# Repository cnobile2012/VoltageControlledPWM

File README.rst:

***************************************
Voltage-Controlled PWM Motor Controller
***************************************
The MIT License (MIT)

This circuit can supply either a 3.3 or 5 volt logic level PWM signal
depending on the reference voltage used. The voltage control input can also
be driven with either a 3.3 or 5 volt logic level signal depending on the
how the circuit is calibrated.

The PWM frequency can be adjusted in the range of 25K Hertz.

=======
LTspice
=======

Spice files for testing the circuit viability.

=====
KiCAD
=====

KiCAD files of the schematic and PCB.

========================
Calibration Instructions
========================

Test Equipment
--------------

  1. +12 and -12 Volt bench power supply.
  2. +5 or +3.3 Volt bench power supply.
  3. Variable voltage bench supply (0V-3.3V or 0V-5V).
  4. Multimeter
  5. Oscilloscope
  6. Frequency Counter (Optional--Can use the scope)

First, be sure your dual voltage power supply is as close to +12 and -12 volts
as possible. This will also be true in the actual environment that this PWM
will call home. If there is a slight offset between the absolute + and -
voltages there will also be a slight offset between the internal zero crossing
point of the triangle wave. Resistor R6 (460) can be adjusted to compensate for
this. The two trimmers R9 and R11 can also affect a slightly off zero crossing
by adjusting the complete on or off of the PWM, that is where a 0 control
voltage causes the output PWM to be 0 volts and the max 3.3/5 control voltage
causes the PWM to be 3.3/5 volts.

Calibration
-----------

  1. The R3 trimmer is used to adjust the internal triangle reference voltage.
     This should nominally be 10 volts peak-to-peak with the trimmer set to
     approximately 250K. Put your scope probes between TP2 (Triangle Wave) and
     TP0 (GND) then adjust R3.
  2. The R1 trimmer is used to adjust the frequency of the triangle wave. This
     should nominally be 25K Hertz with the trimmer set to approximately 24K.
     Put your scope or frequency counter probes between TP2 (Triangle Wave)
     and TP0 (GND) then adjust R1.
  3. The R9 trimmer is used to adjust the symmetry of the sweep voltage. This
     is the Control Voltage that adjusts the modulation of the PWM frequency.
     Adjust the variable power supply to 50% of 3.3V (1.65V) or 5V (2.5V)
     depending on your drive voltage then attach the supply to J3 and attach
     the multimeter probes to TP3 (Sweep) and TP0 (GND). Double check that the
     supply voltage is at 50% of your driving voltage then adjust R9 so the
     voltage on the multimeter is as close to 0 (zero) volts as possible.
  4. The R11 trimmer is used to set the peak-to-peak of the sweep voltage. Set
     the variable power supply to your drive voltage 5V or 3.3V and attach it
     to J3 (Voltage Control Input). Attach the multimeter probes to TP3 (Sweep)
     and TP0 (GND). Adjust R11 so that the multimeter shows plus 5V. Adjust the
     supply to 0 (zero) volts (or short the two pins on J3) and check that the
     voltage on the multimeter is -5V. See note 1 below.
  5. Check the PWM. Adjust the supply voltage to 50% as was done in step 3
     above and check that the PWM is 50%, then adjust the supply to 0 (zero)
     (or just short the two pins on J3) Check that the PWM is 0 (zero) volts.

Notes:

  1. In order to get 0 (full off) and 5/3.3 Volts (full on), on the PWM the
     sweep voltage may need to be slightly more than 10V peak-to-peak (R11)
     assuming the maximum triangle wave voltage is still 10V
     peak-to-peak. Adjusting the zero crossing with R9 may also be necessary.
  2. TP1 provides a square wave output, however it is not used in any of the
     calibrations.
  3. On Version 1.0 of the PCB the silk screen for the TPs (test points) are
     rather small and difficult to read. This will be fixed in version 2.0 of
     the PCB. The photos below should help with identifying which TP is which.

==============
PCBs Version 1
==============

.. image:: images/VoltageControlledPWM-V1.0-front.jpg
  :width: 400
  :alt: Circuit board frontside image

.. image:: images/VoltageControlledPWM-V1.0-back.jpg
  :width: 400
  :alt: Circuit board backside image

=========
Schematic
=========

.. image:: images/VoltageControlledPWM-V1.0.png
  :width: 400
  :alt: Schematic

I want to give attribution to `Zero999 <https://www.eevblog.com/forum/beginners/simple-analog-function-generator-design/msg1174983/#msg1174983>`_
for the oscillator part of my circuit.

Feel free to contact me at: carl dot nobile at gmail.com

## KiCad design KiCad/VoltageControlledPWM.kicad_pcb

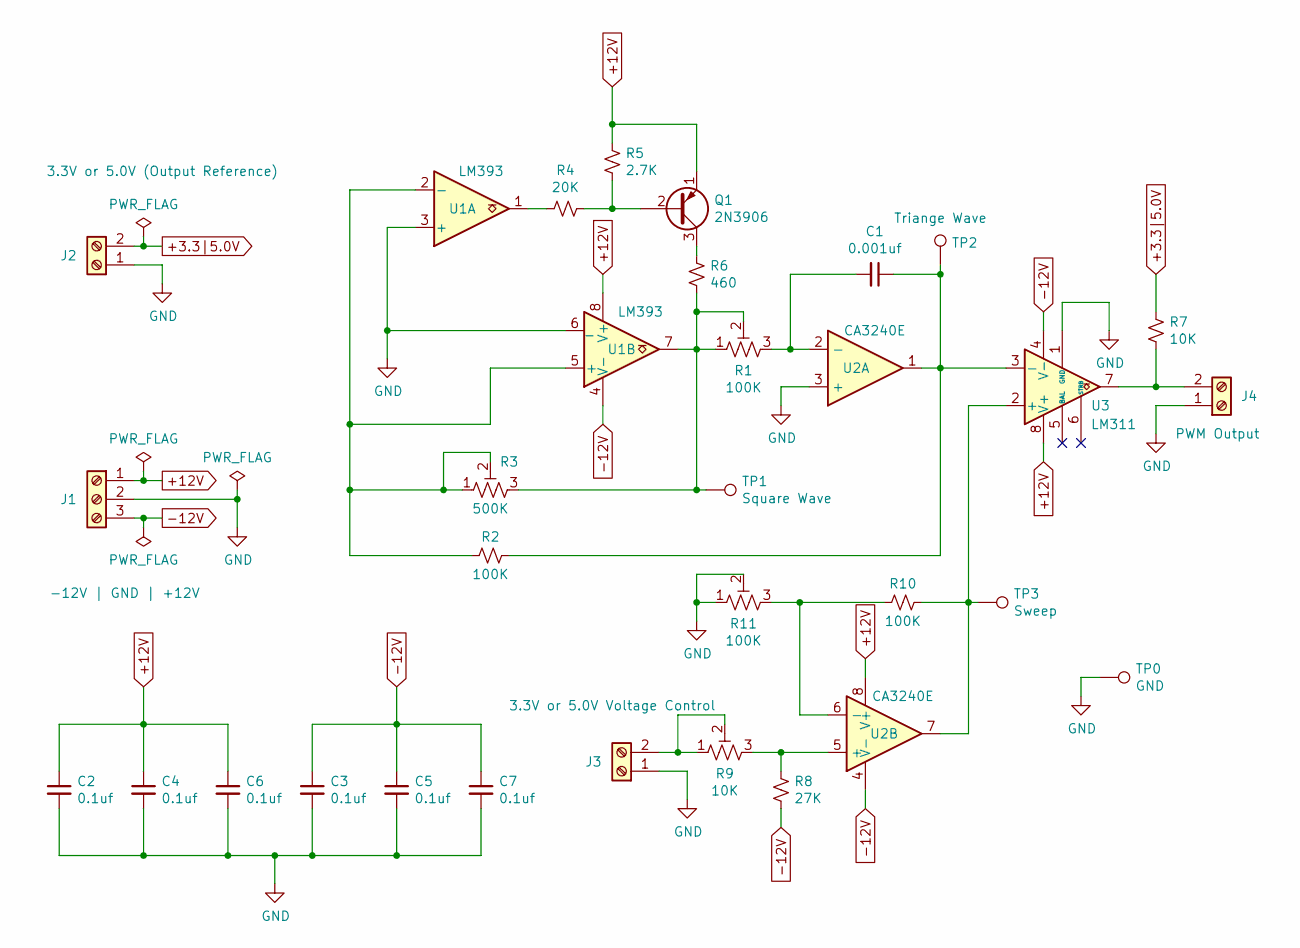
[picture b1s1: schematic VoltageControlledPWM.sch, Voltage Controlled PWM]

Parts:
C1: 0.001uf; C_Disc_D4.7mm_W2.5mm_P5.00mm
C2, C3, C4, C5, C6, C7: 0.1uf; C_Disc_D4.7mm_W2.5mm_P5.00mm
J1: -12V | GND | +12V; TerminalBlock_Phoenix_MKDS-1,5-3-5.08_1x03_P5.08mm_Horizont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
J2: 3.3V or 5.0V (Output Reference); TerminalBlock_Phoenix_MKDS-1,5-2-5.08_1x02_P5.08mm_Horizont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
J3: 3.3V or 5.0V Voltage Control; TerminalBlock_Phoenix_MKDS-1,5-2-5.08_1x02_P5.08mm_Horizont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
J4: PWM Output; TerminalBlock_Phoenix_MKDS-1,5-2-5.08_1x02_P5.08mm_Horizont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
Q1: 2N3906; TO-92_Inline
R1, R11: 100K; Potentiometer_Bourns_3296W_Vertical
R2, R10: 100K; R_Axial_DIN0207_L6.3mm_D2.5mm_P10.16mm_Horizontal
R3: 500K; Potentiometer_Bourns_3296W_Vertical
R4: 20K; R_Axial_DIN0207_L6.3mm_D2.5mm_P10.16mm_Horizontal
R5: 2.7K; R_Axial_DIN0207_L6.3mm_D2.5mm_P10.16mm_Horizontal
R6: 460; R_Axial_DIN0207_L6.3mm_D2.5mm_P10.16mm_Horizontal
R7: 10K; R_Axial_DIN0207_L6.3mm_D2.5mm_P10.16mm_Horizontal
R8: 27K; R_Axial_DIN0207_L6.3mm_D2.5mm_P10.16mm_Horizontal
R9: 10K; Potentiometer_Bourns_3296W_Vertical
TP0: GND; TestPoint_Loop_D2.50mm_Drill1.0mm
TP1: Square Wave; TestPoint_Loop_D2.50mm_Drill1.0mm
TP2: Triange Wave; TestPoint_Loop_D2.50mm_Drill1.0mm
TP3: Sweep; TestPoint_Loop_D2.50mm_Drill1.0mm
U1: LM393; SO-8_3.9x4.9mm_P1.27mm
U2: CA3240E; DIP-8_W7.62mm
U3: LM311; DIP-8_W7.62mm

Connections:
+3.3|5.0V: J2.2, R7.1
+12V: C2.1, C4.1, C6.1, J1.1, Q1.1 (E), R5.1, U1.8 (V+), U2.8 (V+), U3.8 (V+)
-12V: C3.1, C5.1, C7.1, J1.3, R8.2, U1.4 (V-), U2.4 (V-), U3.4 (V-)
GND: C2.2, C3.2, C4.2, C5.2, C6.2, C7.2, J1.2, J2.1, J3.1, J4.1, R11.1, R11.2, TP0.1, U1.3 (+), U1.6 (_), U2.3 (+), U3.1 (GND)
unnamed: C1.1, R2.1, TP2.1, U2.1, U3.3 (-)
unnamed: C1.2, R1.3, U2.2 (-)
unnamed: J3.2, R9.1, R9.2
unnamed: J4.2, R7.2, U3.7
unnamed: Q1.2 (B), R4.1, R5.2
unnamed: Q1.3 (C), R6.1
unnamed: R1.1, R1.2, R3.3, R6.2, TP1.1, U1.7
unnamed: R2.2, R3.1, R3.2, U1.2 (-), U1.5 (+)
unnamed: R4.2, U1.1
unnamed: R8.1, R9.3, U2.5 (+)
unnamed: R10.1, TP3.1, U2.7, U3.2 (+)
unnamed: R10.2, R11.3, U2.6 (-)

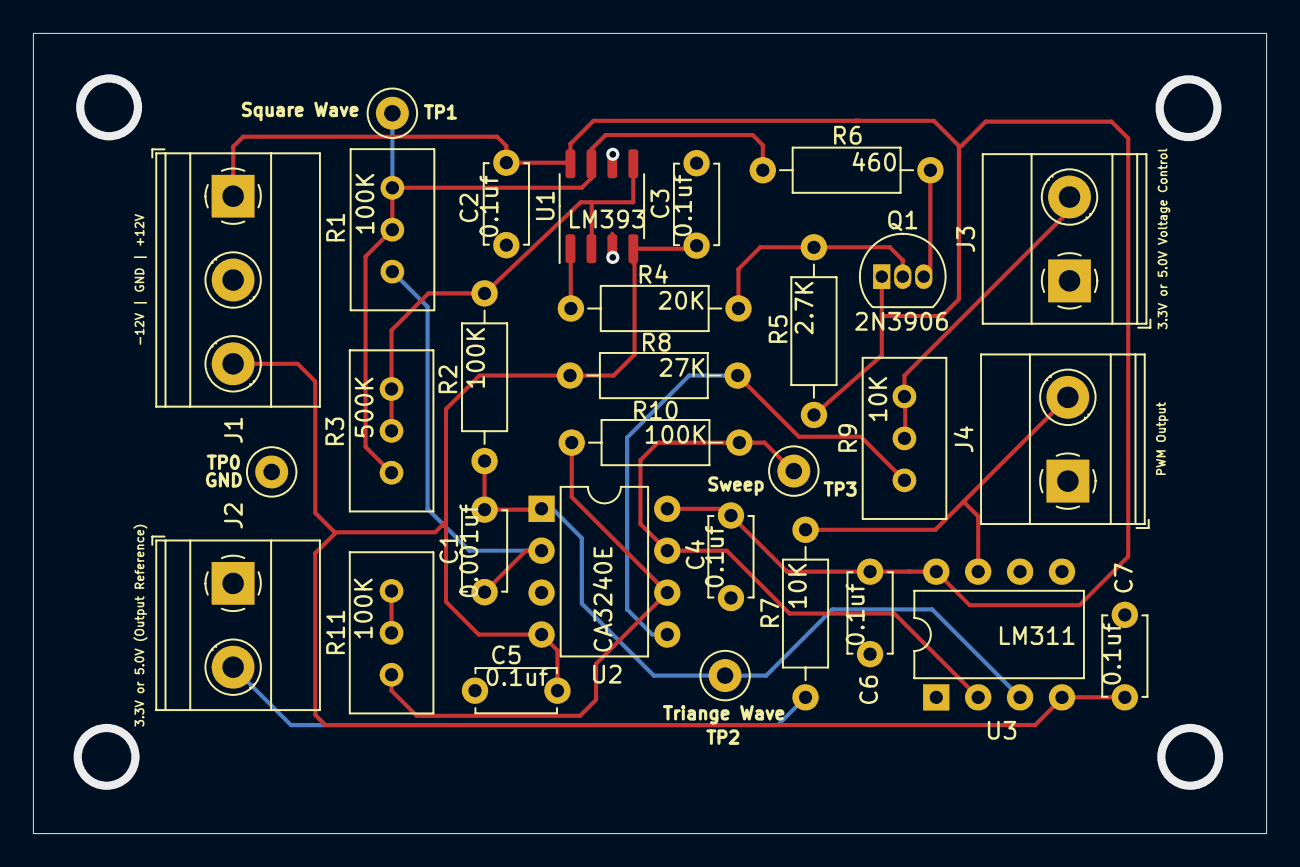
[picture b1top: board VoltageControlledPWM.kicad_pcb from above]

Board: 2 copper layers, 74.8 x 48.5 mm, 30 parts (0 on the bottom side), 16 nets.

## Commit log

2021-07-18 Initial commit.
2021-07-20 Latest updates
2021-07-21 Updated the README.
2021-07-21 Updated to the board.
2021-07-21 Added the schematic PDF file. and updated .gitignore.
2021-07-21 Added an image file.
2021-07-21 Fixed the file name in the README.
2021-07-21 Added Logos.
2021-07-24 Fixed some spelling and grammar issues.
2021-08-07 Removed 'fp-info-cache' from the remo.
2021-08-07 Added images for the PCBs, updated both the README and the .gitignore files, and a minor update the LTSpice file.
2021-08-07 Added a description of what this cercuit is. Duh
2021-08-07 Got rid of the bold type in the notes.
2021-08-07 Updated the calibration instructions again.
2021-08-07 Updated the calibration instructions yet again.
2021-08-07 Added attribution for the ocilator part of my circuit.
2021-08-07 Fixed the version numbers.
2021-08-08 Fixes for version 2.0. Changed the direction of increase voltage on R9 and R11. Increased silkscreen size of TPs.
